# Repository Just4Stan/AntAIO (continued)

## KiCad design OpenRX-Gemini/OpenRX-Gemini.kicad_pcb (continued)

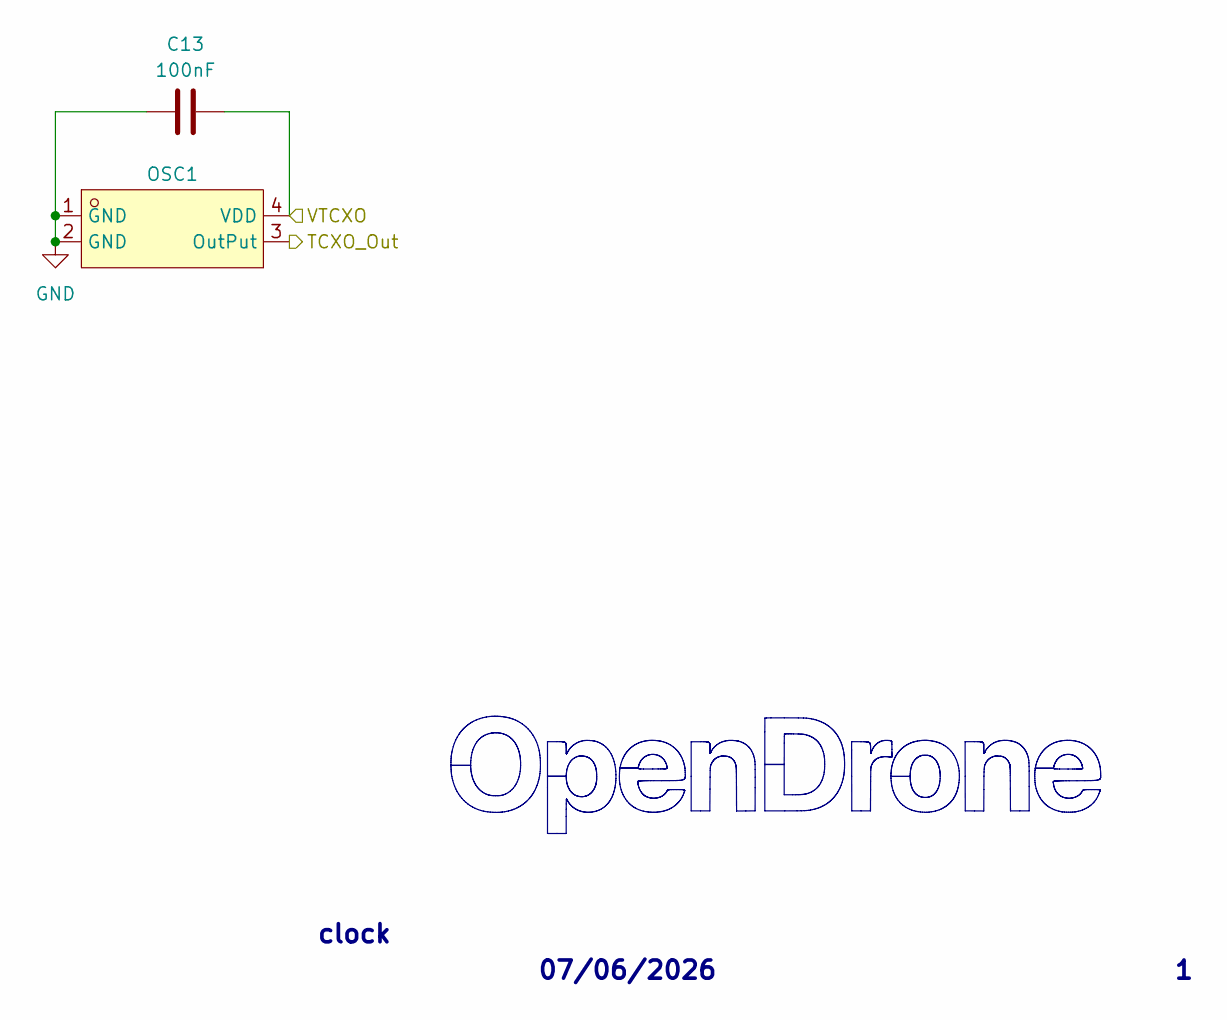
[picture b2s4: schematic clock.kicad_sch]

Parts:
C13: 100nF; C_0201_0603Metric; LCSC C76939
OSC1: OW7EL89CENUYO3YLC-32M; OSC-SMD_4P-L2.0-W1.6-BL_TXC_7Z; LCSC Part C22381772

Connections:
/Clock/TCXO_Out: OSC1.3 (OutPut); also elsewhere on the board
/Clock/VTCXO: C13.2, OSC1.4 (VDD); also elsewhere on the board
GND: C13.1, OSC1.1 (GND), OSC1.2 (GND); also elsewhere on the board

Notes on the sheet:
07/06/2026
clock

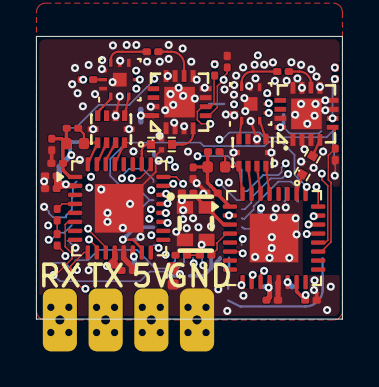
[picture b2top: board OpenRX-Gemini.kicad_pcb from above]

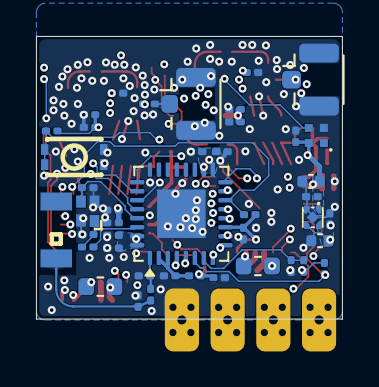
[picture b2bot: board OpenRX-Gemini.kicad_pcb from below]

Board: 6 copper layers, 17.0 x 15.7 mm, 85 parts (44 on the bottom side), 69 nets.

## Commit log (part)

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2026-05-08 OpenRX Lite (UFL + molex)
2026-05-13 add via testing board
2026-06-07 annotate
2026-06-10 fab/BOM/cpl as ordered
2026-06-10 updated HW files as ordered
